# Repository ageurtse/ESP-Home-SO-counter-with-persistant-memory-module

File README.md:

# ESP Home, SO 4 channel counter with P1 interface

<center></center>

I wrote this software and developed the hardware because i was in the need of a device which could count my pulses from a water meter and from my solar pannels. 
The default counter from within ESPHome does the thrick, one could also preserve te counted value in the memory off a ESP device. 
But on my electrical meter which counts 2000 pulses per kW it will wearout in a couple of days. 

So i wen't searching and found this beaty which doesn't coast that much at all. 
https://www.adafruit.com/product/1895

After finding the device i need a way to use it in home assistant, that was for me as a hobby programmer the hardes part, first search for a library which could do the trick. 
and second how to interface the library with ESPHome so i could use it. 

For the library a big thanks to @RobTillart for his great library https://github.com/RobTillaart/FRAM_I2C which i'm implementing in it. 

I'm still working on a test setup, next step is to develop a need 4 wat SO circuit and PCB so one could rebuild.

I found a realy big bug in the hardware, the fourth SO input can't be working, becaus off pulling down the TX inpunt on the ESP8266. When pulling this one down at boot, the device won't boot.

## Description about the FRAM module.

FRAM stands for Ferroelectric RAM - https://en.wikipedia.org/wiki/Ferroelectric_RAM

FRAM memory is much faster than EEPROM and almost as fast as (Arduino UNO) RAM. Another important feature FRAM has in common with EEPROM is that FRAM keeps its content after a reboot as it is non-volatile, even for years. That makes it ideal to store configuration or logging data in a project.
## Operational

There are 2 parts that one should keep in mind.

**First:**
One should make use off i2cfram.h this is the interface file between ESPHome and the library from https://github.com/RobTillaart/FRAM_I2C
in this file there is a setup part, where at boot the device is looking for a memory module and initializes it. 
further there are 2 function which could be called from within Lambda

float readfromfram(uint32_t memaddr), which reads from the given adres slot and returns a float value
void writetofram(uint32_t memaddr, float value), writes a float to the given memory slot
because of the use of floats in ESPhome, every memory slot contains 4 bytes. so if one give memaddr 10, it will write or read 4 bytes from addres 40

**Second:**
This is the yaml file.
For every counter i make use of a global variabel, which will be loaded from memory at boot time. 
It is also posible to (re)set te counters from Homeassistant. 

I disabled the timout so one could use the device without home assistant, i did a test run of 2 days without problems. 

There is the need for the custom component to initializes the memory module. 

From within the binary sensor, the global value is added with 1 at a time, on every count the new value is written to the memory module.

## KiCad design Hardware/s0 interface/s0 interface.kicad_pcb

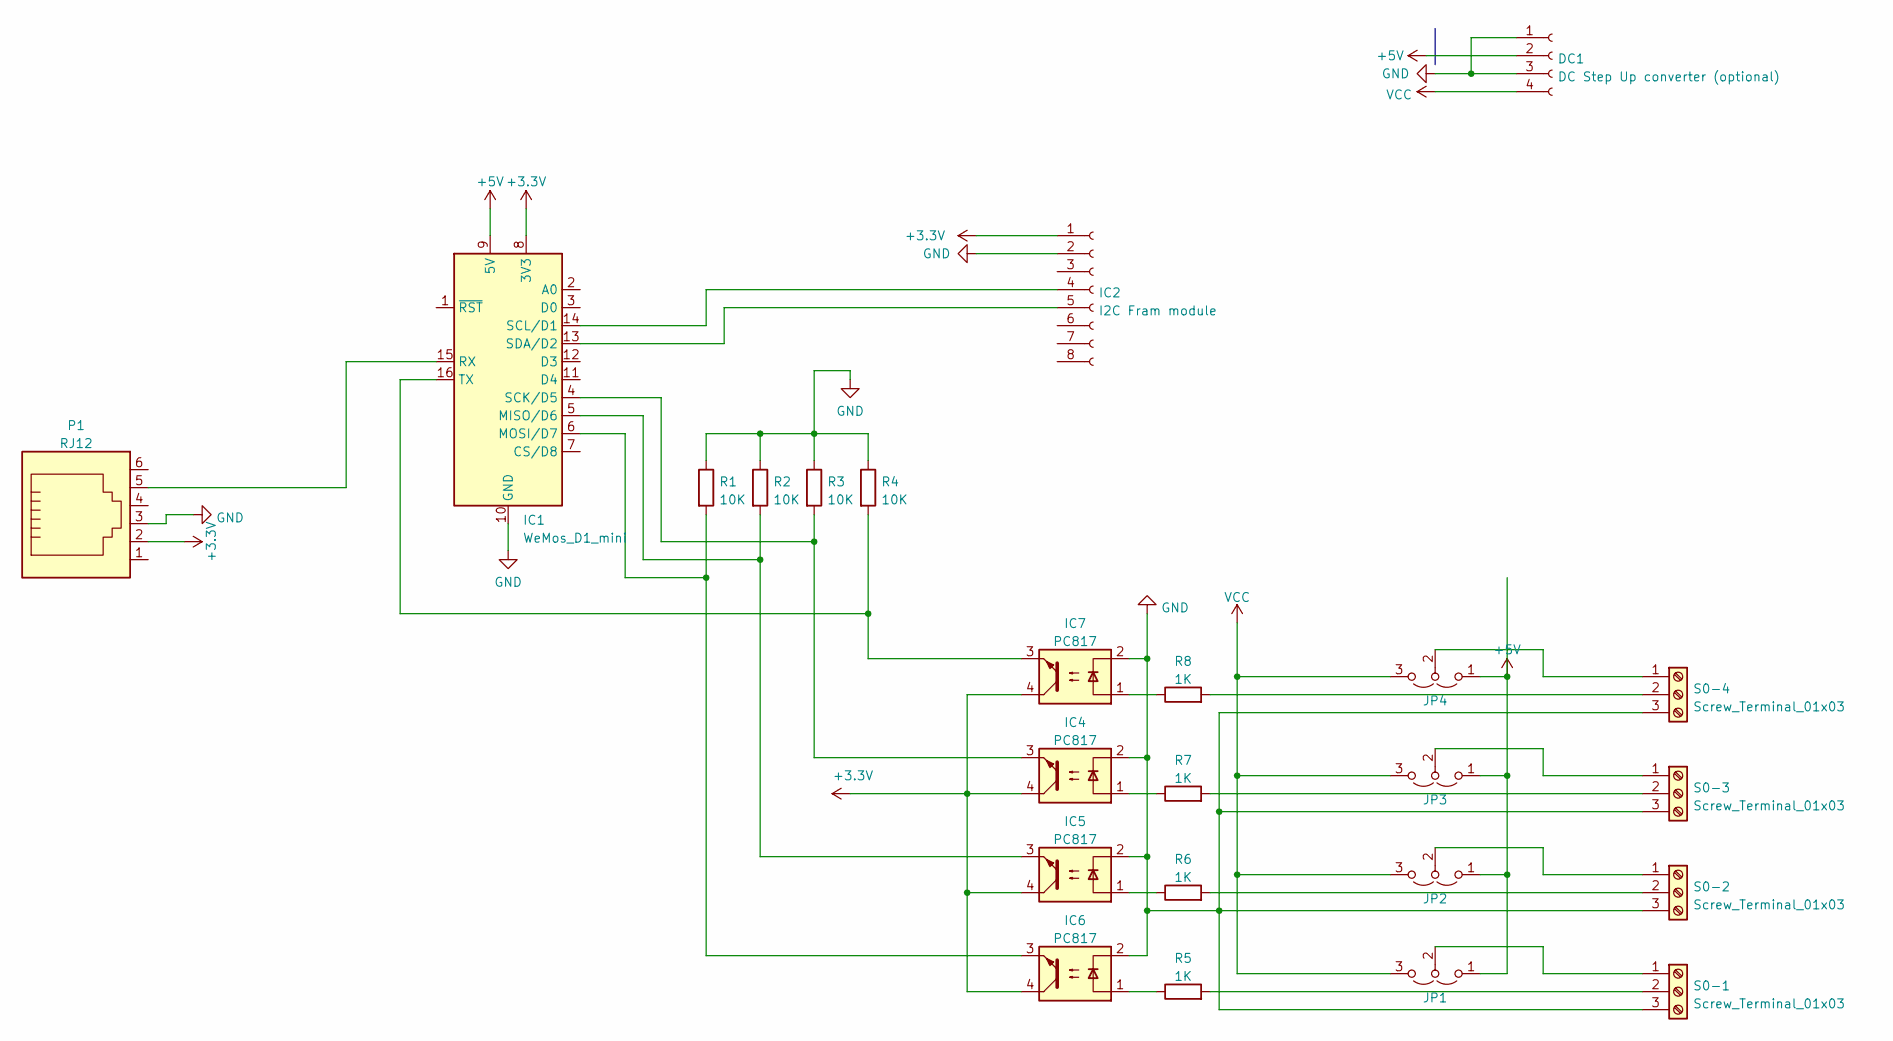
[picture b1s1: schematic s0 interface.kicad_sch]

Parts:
DC1: DC Step Up converter (optional); dcdc converter
IC1: WeMos_D1_mini; WEMOS_D1_mini_light
IC2: I2C Fram module; I2C FRAM Board
IC4, IC5, IC6, IC7: PC817; DIP-4_W7.62mm
JP1, JP2, JP3, JP4: Jumper_3_Open; SolderJumper-3_P1.3mm_Open_RoundedPad1.0x1.5mm
P1: RJ12; RJ12_Amphenol_54601
R1, R2, R3, R4: 10K; R_Axial_DIN0207_L6.3mm_D2.5mm_P7.62mm_Horizontal
R5, R6, R7, R8: 1K; R_Axial_DIN0207_L6.3mm_D2.5mm_P7.62mm_Horizontal
S0-1, S0-2, S0-3, S0-4: Screw_Terminal_01x03; TerminalBlock_Phoenix_MKDS-3-3-5.08_1x03_P5.08mm_Horizontal

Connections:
+3.3V: IC1.8 (3V3), IC2.1, IC4.4, IC5.4, IC6.4, IC7.4, P1.2
+5V: DC1.2, IC1.9 (5V), JP1.1 (A), JP2.1 (A), JP3.1 (A), JP4.1 (A)
GND: DC1.1, DC1.3, IC1.10 (GND), IC2.2, IC4.2, IC5.2, IC6.2, IC7.2, P1.3, R1.1, R2.1, R3.1, R4.1, S0-1.3, S0-2.3, S0-3.3, S0-4.3
unnamed: IC1.4 (SCK/D5), IC4.3, R3.2
unnamed: IC1.5 (MISO/D6), IC5.3, R2.2
unnamed: IC1.6 (MOSI/D7), IC6.3, R1.2
unnamed: IC1.13 (SDA/D2), IC2.5
unnamed: IC1.14 (SCL/D1), IC2.4
unnamed: IC1.15 (RX), P1.5
unnamed: IC1.16 (TX), IC7.3, R4.2
unnamed: IC4.1, R7.1
unnamed: IC5.1, R6.1
unnamed: IC6.1, R5.1
unnamed: IC7.1, R8.1
unnamed: JP1.2 (C), S0-1.1
unnamed: JP2.2 (C), S0-2.1
unnamed: JP3.2 (C), S0-3.1
unnamed: JP4.2 (C), S0-4.1
unnamed: R5.2, S0-1.2
unnamed: R6.2, S0-2.2
unnamed: R7.2, S0-3.2
unnamed: R8.2, S0-4.2
VCC: DC1.4, JP1.3 (B), JP2.3 (B), JP3.3 (B), JP4.3 (B)

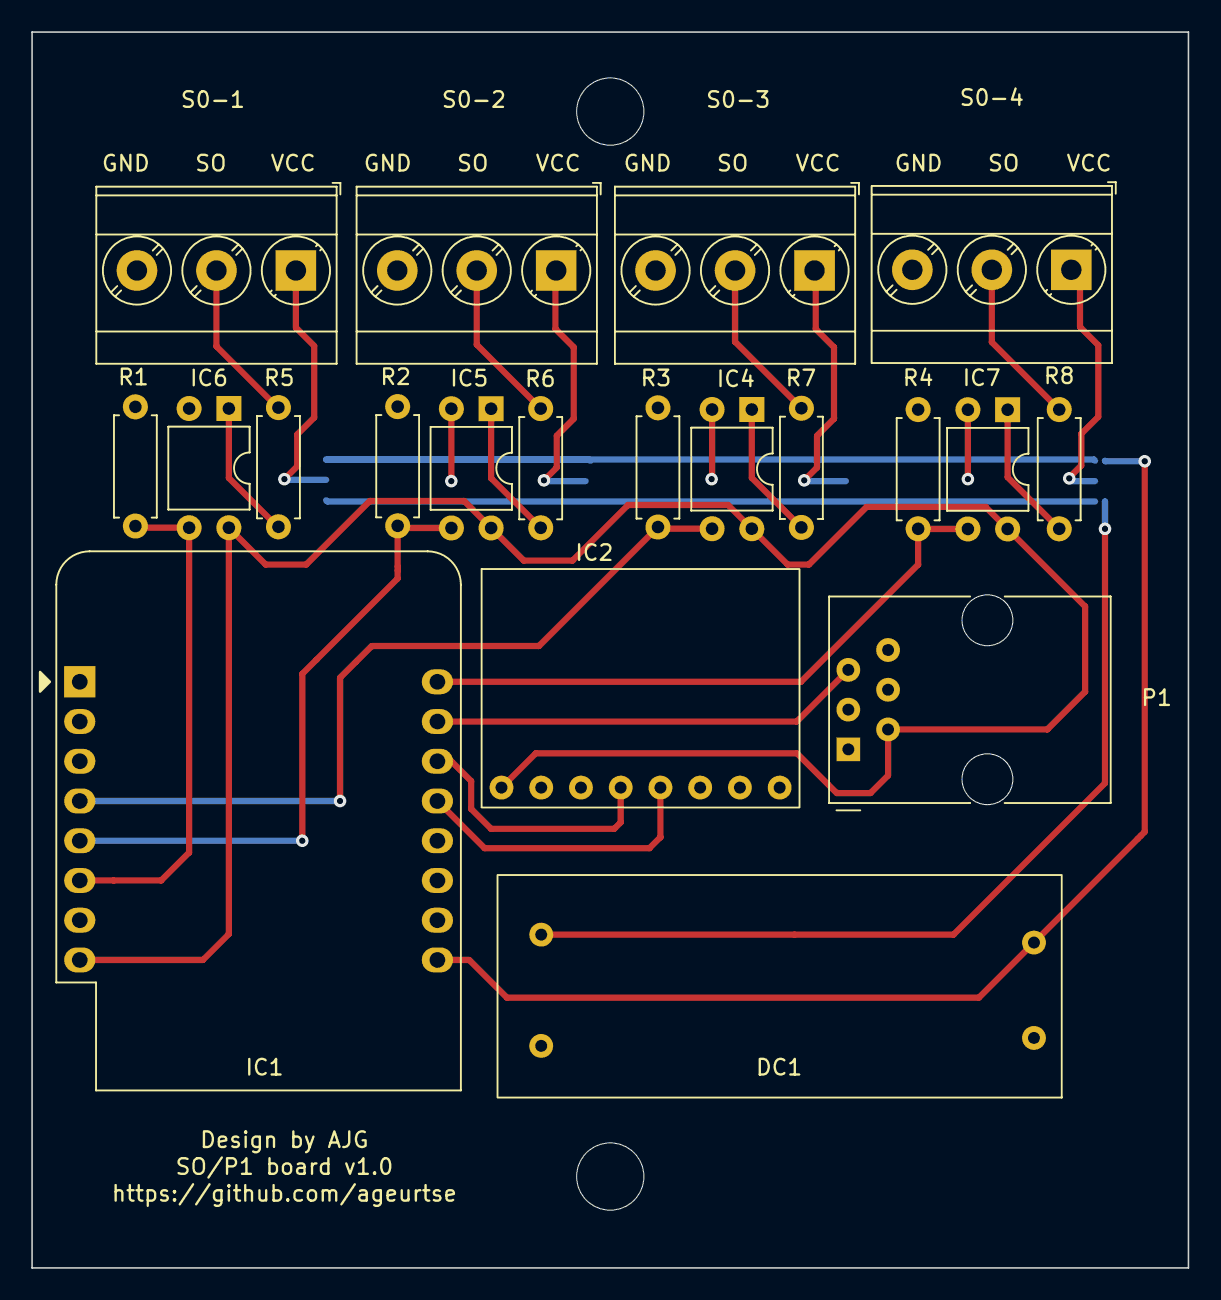
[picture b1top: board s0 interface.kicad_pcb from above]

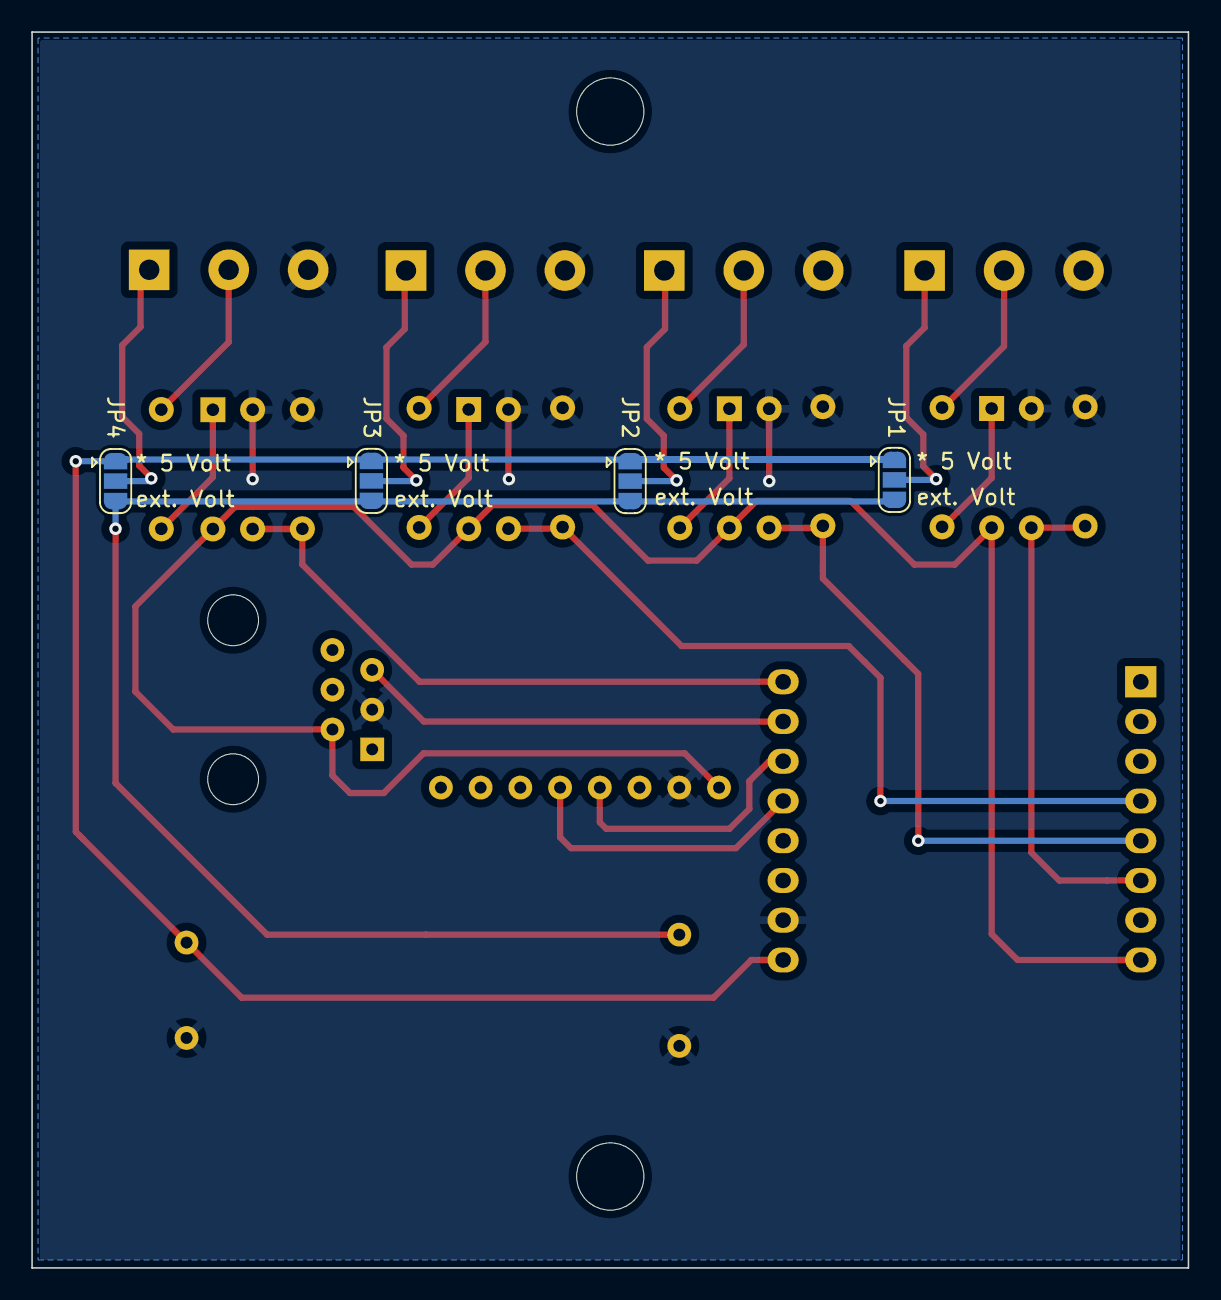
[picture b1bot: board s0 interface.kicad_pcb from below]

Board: 2 copper layers, 73.9 x 79.0 mm, 24 parts (4 on the bottom side), 23 nets.

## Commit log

2022-12-27 Add files via upload
    First upload of the files, it is all in a test stage, working is stil in progress, need to comment stuff inside the files.
    Later on try to make some hardware to runt it on, hardware should be good for 4 or 8 so inputs.
2022-12-28 Update README.md
    change link to fram package
2022-12-30 Update README.md
    Update the readme file
2022-12-30 float updates
    Float write has been updated in the primary library, big thanks to Robtillart.
    therefor some small modification
2022-12-30 typo
2023-01-07 hardware
    added hardware and update software
2023-01-07 Create s0 interface front.png
    uploade image
